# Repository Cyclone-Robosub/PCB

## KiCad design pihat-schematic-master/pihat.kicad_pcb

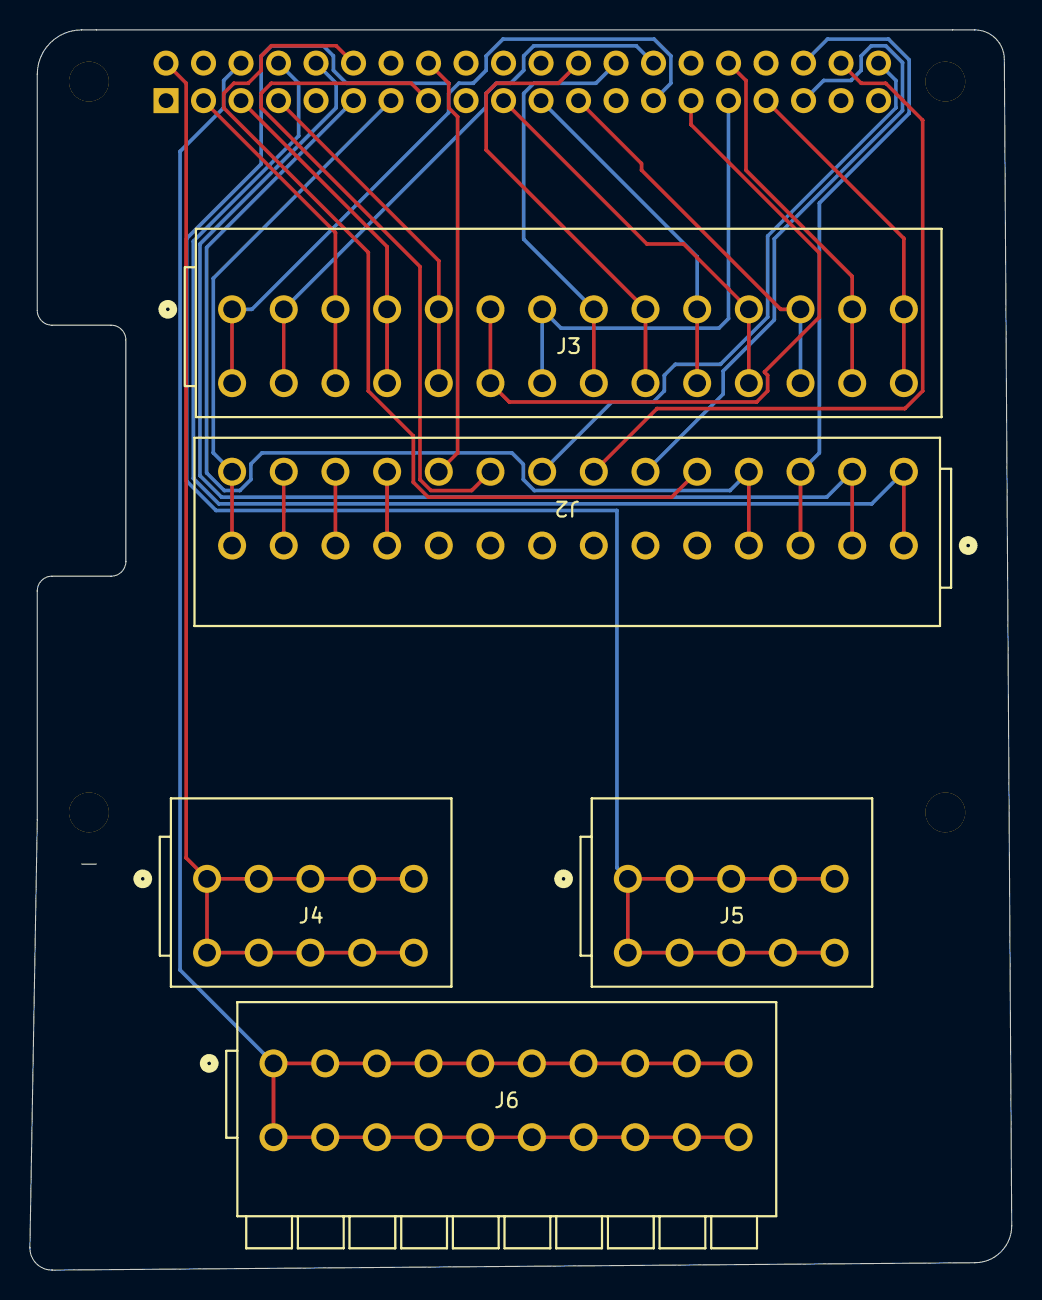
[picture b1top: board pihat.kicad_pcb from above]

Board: 2 copper layers, 66.5 x 84.0 mm, 6 parts (1 on the bottom side), 31 nets.

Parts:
J1: Raspberry_Pi_2_3; PinSocket_2x20_P2.54mm_Vertical
J2, J3: 2601-3114; CONN14_2601-3114_WAG
J4: 5V_Connect; CONN5_2601-3105_WAG
J5: 3V_Connect; CONN5_2601-3105_WAG
J6: 2601-1110; CONN10_2601-1110_WAG

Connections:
unnamed: J1.7 (GCLK0/GPIO4), J3.9 (5_1), J3.10 (5_2)
unnamed: J1.29 (GCLK1/GPIO5), J3.11 (6_1), J3.12 (6_2)
unnamed: J1.31 (GCLK2/GPIO6), J3.13 (7_1), J3.14 (7_2)
unnamed: J1.8 (GPIO14/TXD), J2.1 (1_1), J2.2 (1_2)
unnamed: J1.10 (GPIO15/RXD), J2.3 (2_1), J2.4 (2_2)
unnamed: J1.36 (GPIO16), J2.5 (3_1), J2.6 (3_2)
unnamed: J1.11 (GPIO17), J2.7 (4_1), J2.8 (4_2)
unnamed: J1.12 (GPIO18/PWM0), J2.9 (5_1), J2.10 (5_2)
unnamed: J1.35 (GPIO19/MISO1), J2.11 (6_1), J2.12 (6_2)
unnamed: J1.38 (GPIO20/MOSI1), J2.13 (7_1), J2.14 (7_2)
unnamed: J1.40 (GPIO21/SCLK1), J2.15 (8_1), J2.16 (8_2)
unnamed: J1.15 (GPIO22), J2.17 (9_1), J2.18 (9_2)
unnamed: J1.16 (GPIO23), J2.19 (10_1), J2.20 (10_2)
unnamed: J1.18 (GPIO24), J2.21 (11_1), J2.22 (11_2)
unnamed: J1.22 (GPIO25), J2.23 (12_1), J2.24 (12_2)
unnamed: J1.37 (GPIO26), J2.25 (13_1), J2.26 (13_2)
unnamed: J1.13 (GPIO27), J2.27 (14_1), J2.28 (14_2)
unnamed: J1.28 (ID_SC/GPIO1), J3.3 (2_1), J3.4 (2_2)
unnamed: J1.27 (ID_SD/GPIO0), J3.1 (1_1), J3.2 (1_2)
unnamed: J1.21 (MISO0/GPIO9), J3.19 (10_1), J3.20 (10_2)
unnamed: J1.19 (MOSI0/GPIO10), J3.21 (11_1), J3.22 (11_2)
unnamed: J1.32 (PWM0/GPIO12), J3.25 (13_1), J3.26 (13_2)
unnamed: J1.33 (PWM1/GPIO13), J3.27 (14_1), J3.28 (14_2)
unnamed: J1.23 (SCLK0/GPIO11), J3.23 (12_1), J3.24 (12_2)
unnamed: J1.5 (SCL/GPIO3), J3.7 (4_1), J3.8 (4_2)
unnamed: J1.3 (SDA/GPIO2), J3.5 (3_1), J3.6 (3_2)
unnamed: J1.24 (~CE0/GPIO8), J3.17 (9_1), J3.18 (9_2)
unnamed: J1.26 (~CE1/GPIO7), J3.15 (8_1), J3.16 (8_2)
unnamed: J1.2 (5V), J1.4 (5V), J4.1 (1_1), J4.2 (1_2), J4.3 (2_1), J4.4 (2_2), J4.5 (3_1), J4.6 (3_2), J4.7 (4_1), J4.8 (4_2), J4.9 (5_1), J4.10 (5_2)
unnamed: J1.1 (3V3), J1.17 (3V3), J5.1 (1_1), J5.2 (1_2), J5.3 (2_1), J5.4 (2_2), J5.5 (3_1), J5.6 (3_2), J5.7 (4_1), J5.8 (4_2), J5.9 (5_1), J5.10 (5_2)
unnamed: J1.6 (GND), J1.9 (GND), J1.14 (GND), J1.20 (GND), J1.25 (GND), J1.30 (GND), J1.34 (GND), J1.39 (GND), J6.1 (1_1), J6.2 (1_2), J6.3 (2_1), J6.4 (2_2), J6.5 (3_1), J6.6 (3_2), J6.7 (4_1), J6.8 (4_2), J6.9 (5_1), J6.10 (5_2), J6.11 (6_1), J6.12 (6_2), J6.13 (7_1), J6.14 (7_2), J6.15 (8_1), J6.16 (8_2), J6.17 (9_1), J6.18 (9_2), J6.19 (10_1), J6.20 (10_2)

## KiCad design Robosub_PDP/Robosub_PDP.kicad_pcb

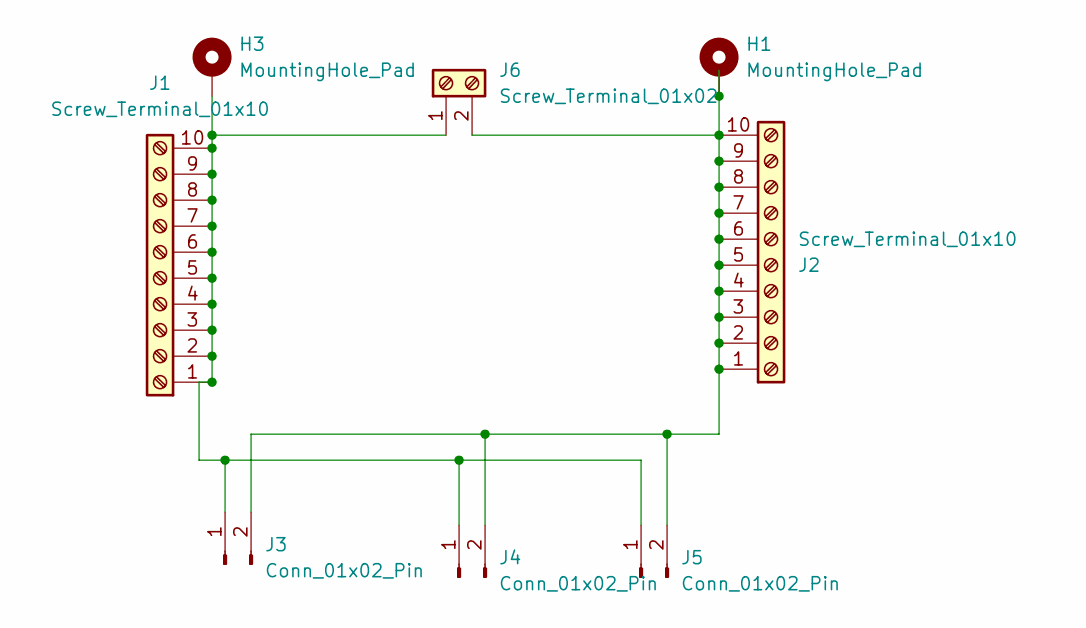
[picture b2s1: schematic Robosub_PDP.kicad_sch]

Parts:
H1, H3: MountingHole_Pad; MountingHole_2.2mm_M2_DIN965_Pad
J1, J2: Screw_Terminal_01x10; TerminalBlock_MaiXu_MX126-5.0-10P_1x10_P5.00mm
J3, J4, J5: Conn_01x02_Pin; JWT_A3963_1x02_P3.96mm_Vertical
J6: Screw_Terminal_01x02; TerminalBlock_MaiXu_MX126-5.0-02P_1x02_P5.00mm

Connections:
unnamed: H3.1, J1.1, J1.2, J1.3, J1.4, J1.5, J1.6, J1.7, J1.8, J1.9, J1.10, J3.1, J4.1, J5.1, J6.1
unnamed: H1.1, J2.1, J2.2, J2.3, J2.4, J2.5, J2.6, J2.7, J2.8, J2.9, J2.10, J3.2, J4.2, J5.2, J6.2

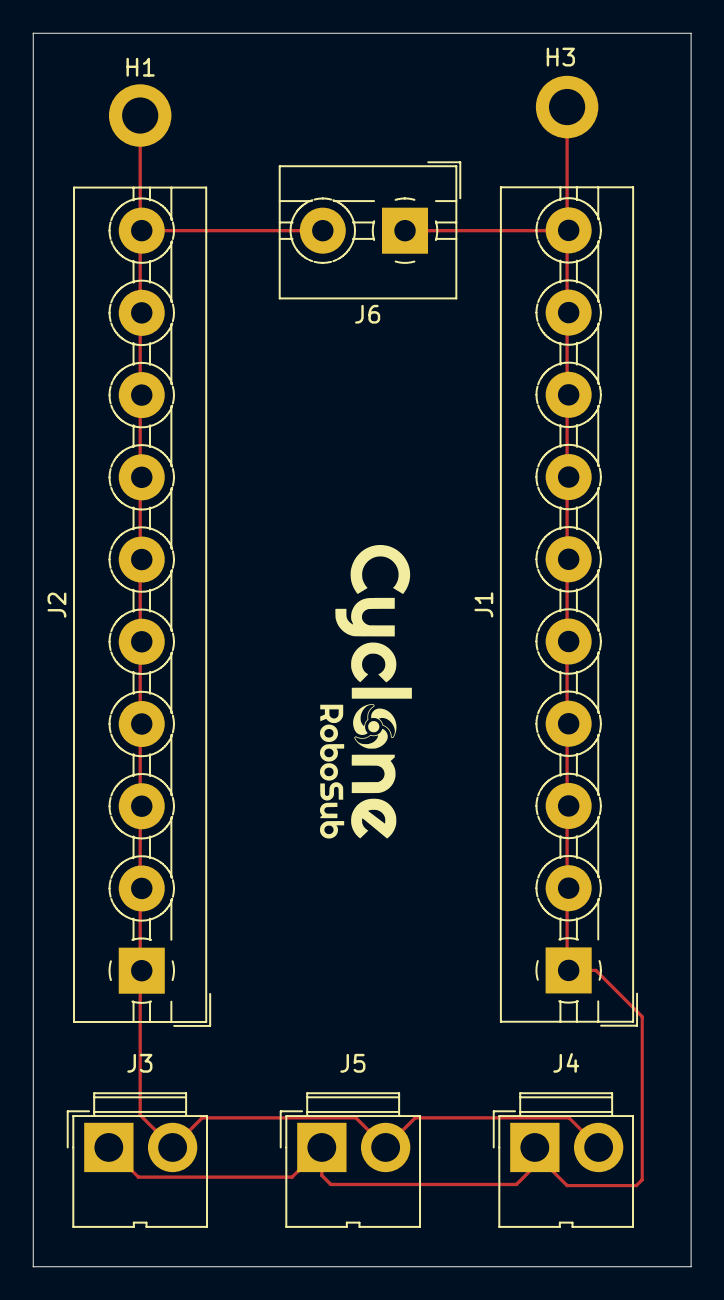
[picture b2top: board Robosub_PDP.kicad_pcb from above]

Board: 2 copper layers, 40.0 x 75.0 mm, 8 parts (0 on the bottom side), 2 nets.

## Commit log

2025-01-13 Adding blank KiCAD project
2025-01-13 test
2025-01-25 Created PDP
2025-01-26 Created PIHAT Prototype
2025-01-26 edited errors and added logo
2025-01-29 idk what is happening??? what is DS_Store????
2025-01-29 idk what is happening. what is DS_Store????
2025-01-29 removed DS_Store
2025-01-29 added .gitignore
2025-01-29 added lck to git ignore
2025-02-01 Began adding Wagos
    I replaced the GPIO connectors with wagos. Will need to download files for shorter wagos to complete the 3.3V, 5V, and Ground Supplies.
2025-02-05 Updates to Pihat
2025-02-08 removed .DS_Store but like fr this time
2025-02-19 Began adding breakout pins
